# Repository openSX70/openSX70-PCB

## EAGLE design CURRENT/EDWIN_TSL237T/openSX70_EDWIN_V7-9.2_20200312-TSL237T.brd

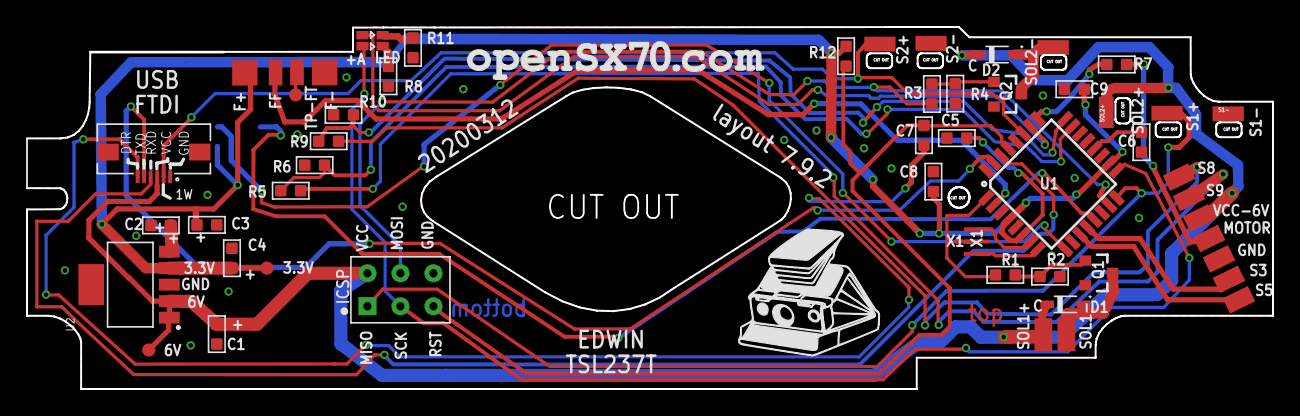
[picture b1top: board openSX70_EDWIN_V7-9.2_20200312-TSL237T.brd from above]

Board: 2 copper layers, 95.9 x 27.9 mm, 44 parts (1 on the bottom side), 35 nets.

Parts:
C1, C4: 10uf; C0603
C2, C3, C5, C6, C7, C8, C9: 100nf; C0603
D1, D2: 1N4148WSF; SODFL2512X100N
ICSP: ICSP; H2X3-2.54
J1: 687106183722
Q1, Q2: 5.8A/30V/35mΩ; SOT23-3
R1, R3, R7: 100R; R0603
R2, R4: 100K 1/10W; R0603
R5, R9: 12K 1/10W; R0603
R6, R10, R12: 10K; R0603
R8, R11: 1K 1/10W; R0603
S1+, S1-, S2+, S2-: SX70-S-PAD-NEW; SX70-S-PAD2
SOL1: SX70-SOLENOID1-2PADS; SX70-SOLENOID1-2
SOL2+, SOL2-: SX70-S-PAD-NEW; SX70-S-PAD2
TP1, TP2, TP3: TEST-POINT3X4; PAD.03X.04
U1: ATMEGA328P_TQFP; TQFP32-08
U2: TPS79501DCQ; SOT127P706X180-6N
U$1: SX70-7-PAD; SX70-7-PAD-PROPER
U$2: FFA; FFA-PAD-PACKAGE
U$3: TSL237T
U$4: LTST-C195KGJRKT; LTST-BILED-15X16
Y1: CSTCE8M00G52Z-R0; CFP95P160X100-3N

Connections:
3.3V: C3.1, C4.2, C5.1, C8.1, C9.1, R12.2, TP2.P$1, U1.4, U1.6, U1.18, U2.4, U$2.F+, U$3.VDD
6V: C1.2, D1.C, D2.C, ICSP.6, J1.3, SOL1.SOL1+, SOL2+.P$1, TP3.P$1, U2.1, U2.2, U$1.VCC
DTR: C7.1, J1.6
FF: U1.2, U$2.FF
GND: C1.1, C2.1, C3.2, C4.1, C5.2, C6.1, C8.2, C9.2, ICSP.4, J1.1, Q1.2, Q2.2, R2.1, R4.1, R6.2, R8.1, R10.2, R11.1, S1-.P$1, S2-.P$1, U1.3, U1.5, U1.21, U2.3, U2.6, U$1.GND, U$2.F-, U$3.GND, Y1.GND
LED1: ICSP.2, U1.17, U$4.P$2
LED2: U1.26, U$4.P$1
LM: U1.9, U$3.OUT
MOTOR+: R7.1, U1.25
MOTOR-HEADER: R7.2, U$1.MOTOR
unnamed: Q1.1, R1.2, R2.2
unnamed: C6.2, U1.20
unnamed: Q2.1, R3.2, R4.2
unnamed: U1.7, Y1.IN
unnamed: TP1.P$1, U$2.FT
unnamed: U1.8, Y1.OUT
unnamed: R8.2, U$4.P$4
unnamed: C2.2, U2.5
unnamed: R11.2, U$4.P$3
OE: U1.13, U$3.OE
RST: C7.2, ICSP.3, R12.1, U1.29
RXD: J1.4, U1.30
S1: ICSP.1, S1+.P$1, U1.16
S3: U1.12, U$1.S3
S5: U1.11, U$1.S5
S8@2.5V: R9.2, R10.1, U1.24
S8@6V: R9.1, U$1.S8
S9@2.5V: R5.2, R6.1, U1.23
S9@6V: R5.1, U$1.S9
SDA_S2: J1.2, S2+.P$1, U1.27
SOL1: R1.1, U1.1
SOL1-: D1.A, Q1.3, SOL1.SOL1-
SOL2: ICSP.5, R3.1, U1.15
SOL2-: D2.A, Q2.3, SOL2-.P$1
TXD: J1.5, U1.31

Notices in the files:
CURRENT/EDWIN_TSL237T/openSX70_EDWIN_V7-9.2_20200312-TSL237T.brd:
Creative Commons "Attribution-NonCommercial 4.0 International (CC BY-NC 4.0)"
https://creativecommons.org/licenses/by-nc/4.0
parts and their libraries:
SparkFun-Connectors: Licensing: Creative Commons ShareAlike 4.0 International - https://creativecommons.org/licenses/by-sa/4.0
